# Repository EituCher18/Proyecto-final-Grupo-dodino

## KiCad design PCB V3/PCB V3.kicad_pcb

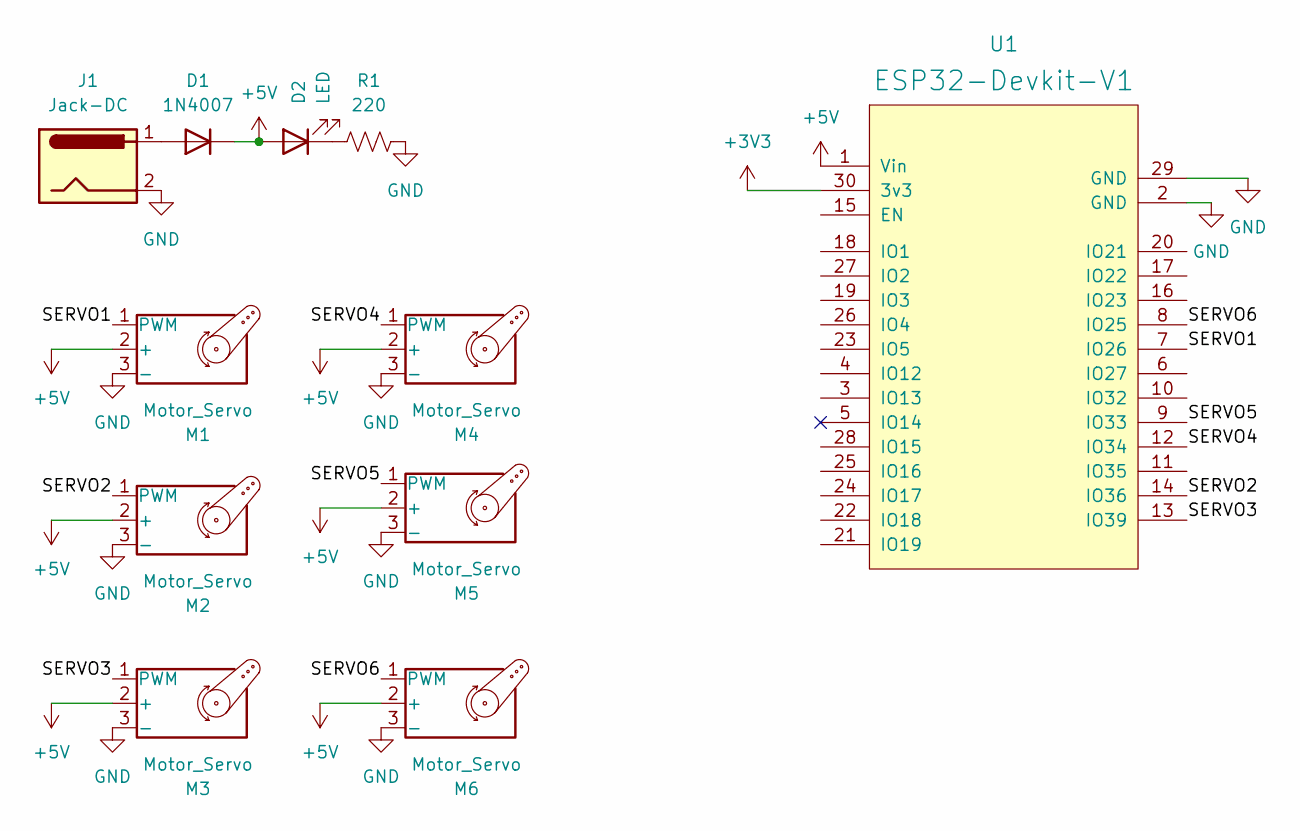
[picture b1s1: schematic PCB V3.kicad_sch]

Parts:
D1: 1N4007; D_DO-41_SOD81_P10.16mm_Horizontal
D2: LED; LED_D5.0mm
J1: Jack-DC; BarrelJack_Horizontal
M1, M2, M3, M4, M5, M6: Motor_Servo; PinHeader_1x03_P2.54mm_Vertical
R1: 220; R_Axial_DIN0309_L9.0mm_D3.2mm_P15.24mm_Horizontal
U1: ESP32-Devkit-V1; DOIT_ESP32_Devkit_mirko

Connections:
+3V3: U1.30 (3v3)
+5V: D1.1 (K), D2.2 (A), M1.2 (+), M2.2 (+), M3.2 (+), M4.2 (+), M5.2 (+), M6.2 (+), U1.1 (Vin)
/SERVO1: M1.1 (PWM), U1.7 (IO26)
/SERVO2: M2.1 (PWM), U1.14 (IO36)
/SERVO3: M3.1 (PWM), U1.13 (IO39)
/SERVO4: M4.1 (PWM), U1.12 (IO34)
/SERVO5: M5.1 (PWM), U1.9 (IO33)
/SERVO6: M6.1 (PWM), U1.8 (IO25)
GND: J1.2, M1.3 (-), M2.3 (-), M3.3 (-), M4.3 (-), M5.3 (-), M6.3 (-), R1.1, U1.2 (GND), U1.29 (GND)
unnamed: D1.2 (A), J1.1
unnamed: D2.1 (K), R1.2

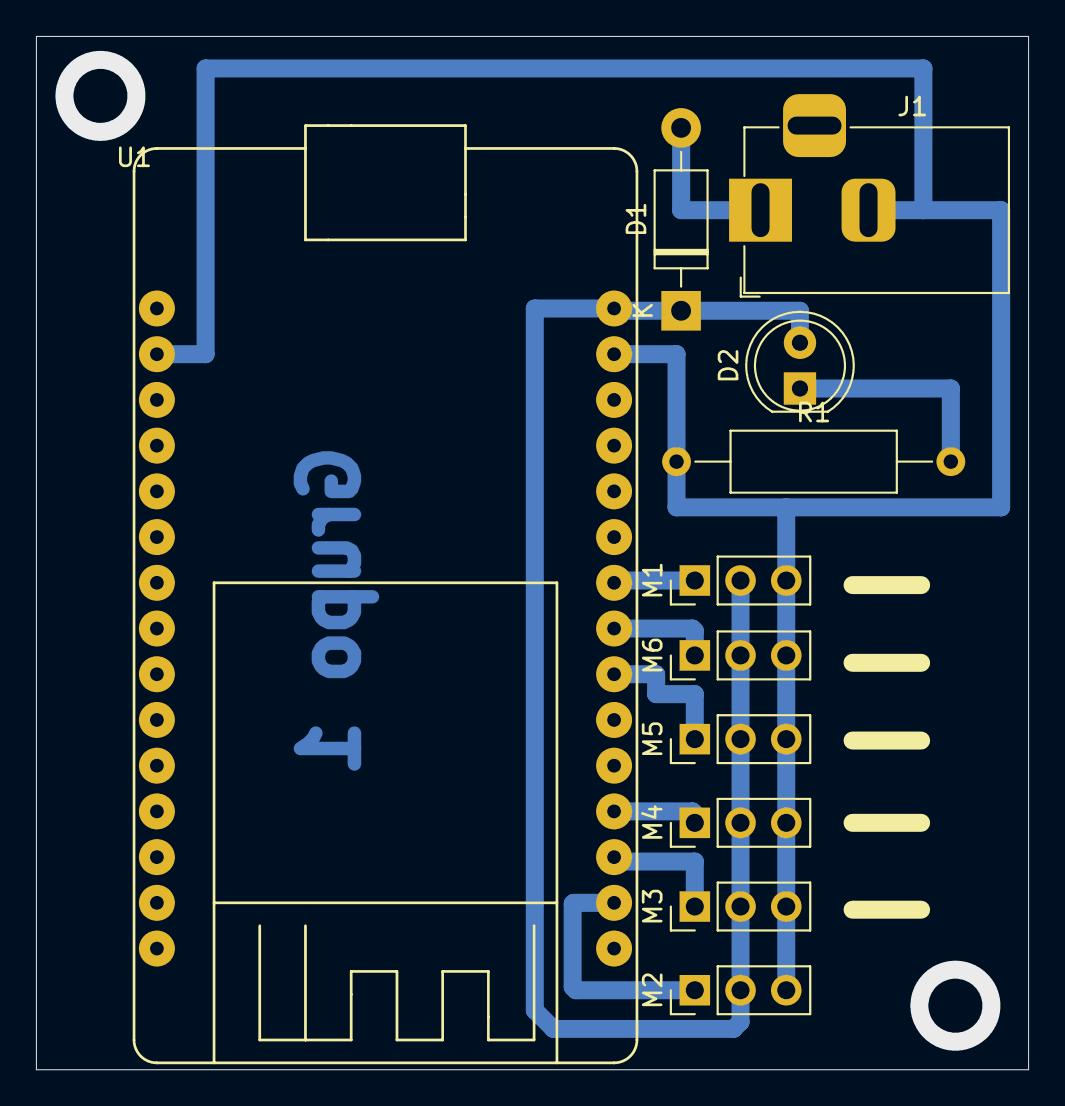
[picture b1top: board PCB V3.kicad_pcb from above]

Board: 2 copper layers, 55.1 x 57.4 mm, 11 parts (0 on the bottom side), 10 nets.

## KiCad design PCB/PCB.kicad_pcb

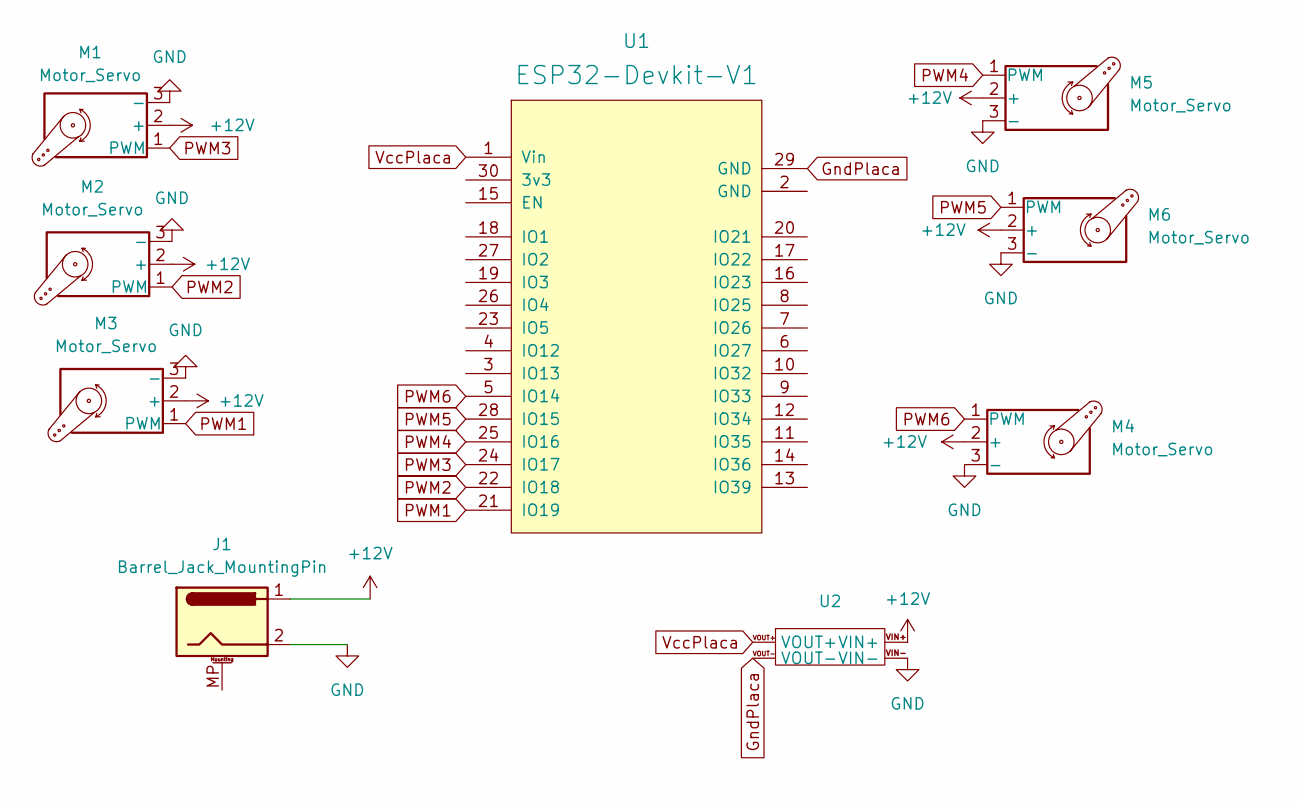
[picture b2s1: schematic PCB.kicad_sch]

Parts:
J1: Barrel_Jack_MountingPin; BarrelJack_CUI_PJ-102AH_Horizontal
M1, M2, M3, M4, M5, M6: Motor_Servo; PinHeader_1x03_P2.54mm_Vertical
U1: ESP32-Devkit-V1; DOIT_ESP32_Devkit_mirko
U2: Step down lm

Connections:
+12V: J1.1, M1.2 (+), M2.2 (+), M3.2 (+), M4.2 (+), M5.2 (+), M6.2 (+), U2.VIN+
GND: J1.2, M1.3 (-), M2.3 (-), M3.3 (-), M4.3 (-), M5.3 (-), M6.3 (-), U2.VIN-
GndPlaca: U1.29 (GND), U2.VOUT-
PWM1: M3.1 (PWM), U1.21 (IO19)
PWM2: M2.1 (PWM), U1.22 (IO18)
PWM3: M1.1 (PWM), U1.24 (IO17)
PWM4: M5.1 (PWM), U1.25 (IO16)
PWM5: M6.1 (PWM), U1.28 (IO15)
PWM6: M4.1 (PWM), U1.5 (IO14)
VccPlaca: U1.1 (Vin), U2.VOUT+

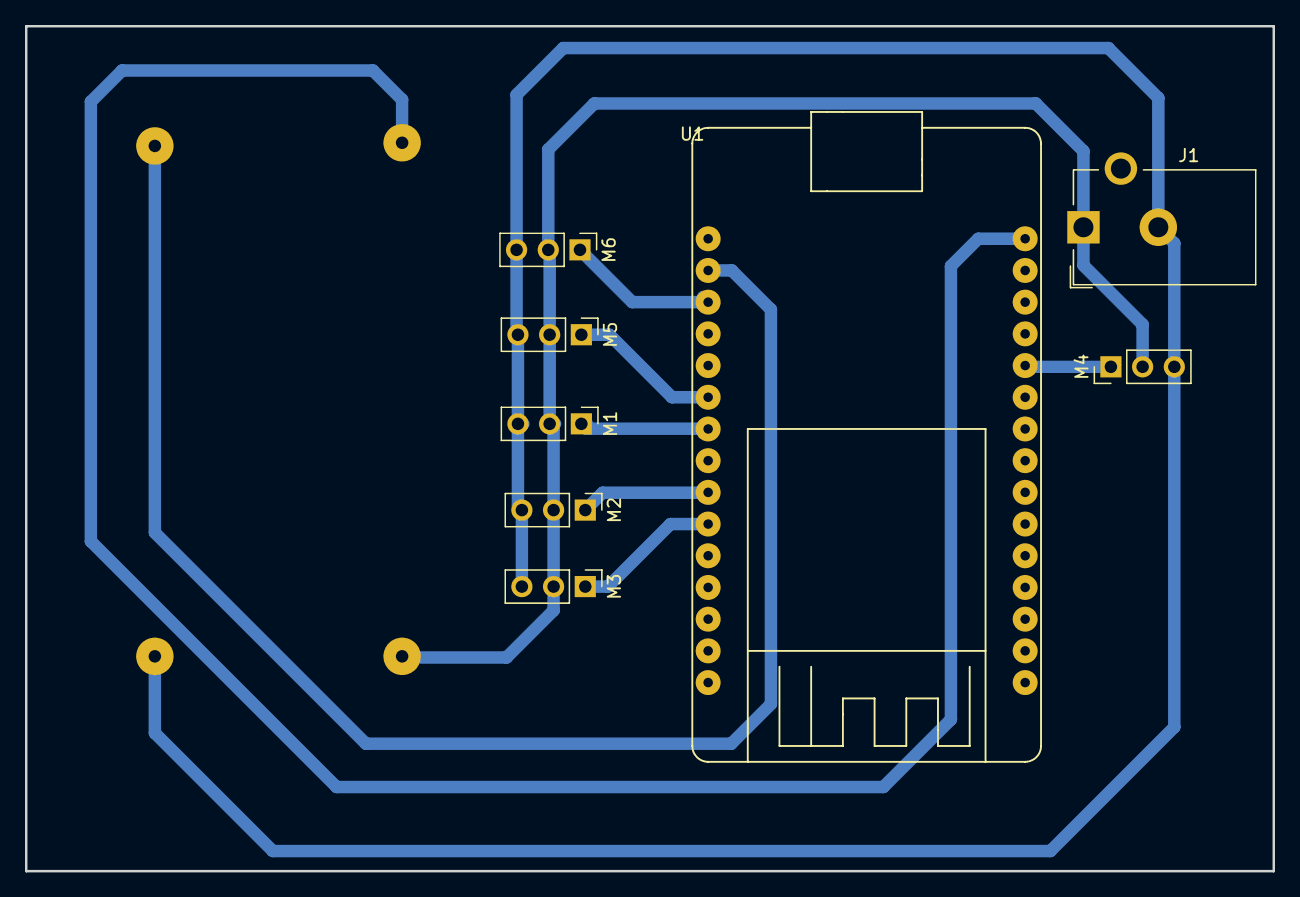
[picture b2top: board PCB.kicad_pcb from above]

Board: 2 copper layers, 100.0 x 67.7 mm, 9 parts (0 on the bottom side), 10 nets.

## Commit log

2024-05-24 Carcasa
2024-05-31 Pcb para imprimir
2024-06-19 Carcasa hecha en Fusion
2024-06-19 Archivos por separado
2024-06-20 Cara de Dodino
2024-07-01 Codigo-1-7-24
2024-07-07 Codigo-de-prueba-Final-2do-bim
2024-08-16 16/8 Compilacion
2024-08-16 Proyecto 16/8 Compilado
2024-09-06 Codigos de prueba
2024-09-06 pines de los servos
2024-09-18 Codigo 17/9
